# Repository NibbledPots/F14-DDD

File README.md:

# F14 DDP
PCB for the DDP/DDD of the F-14 RIO cockpit

You'll have to build and flash it yourself, the code can be found [here](https://github.com/NibbledPots/F14DDPcode)

Includes:
* RDR, IR, and IFF buttons
* PD and Pulse STT, PD Search, RWS, TWS Auto and Manual, and Pulse Search buttons 
* Buttons are in the general shape they are in in the cockpit, but they are not to scale

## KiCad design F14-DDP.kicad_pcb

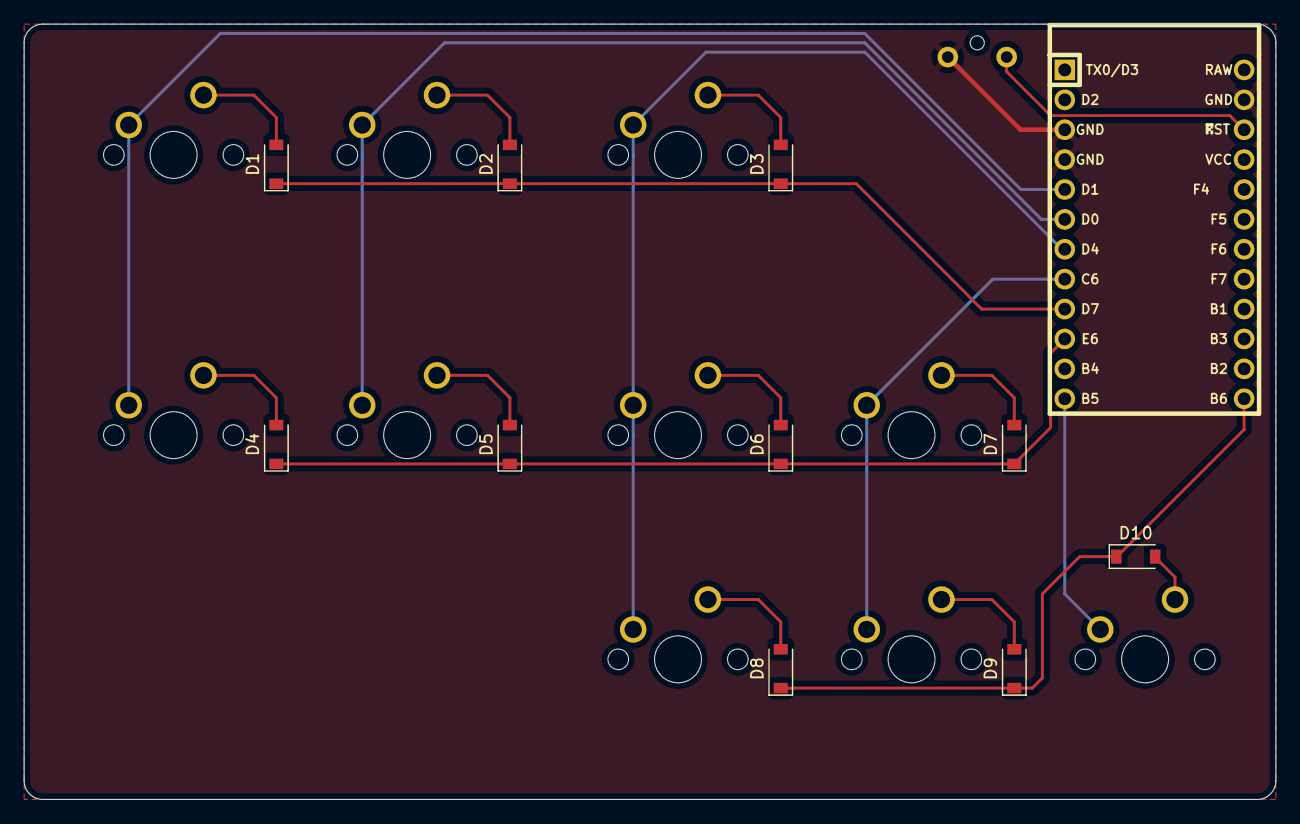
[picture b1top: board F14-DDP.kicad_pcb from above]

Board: 2 copper layers, 106.4 x 65.9 mm, 22 parts (1 on the bottom side), 20 nets.

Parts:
D1, D2, D3, D4, D5, D6, D7, D8, D9, D10: D_Small; D_SOD-123
MX1, MX2, MX3, MX4, MX5, MX6, MX7, MX8, MX9, MX10: MX-NoLED; MXOnly-1U-NoLED
SW1: SW_Push; SW_Tactile_SPST_Angled_MJTP1117-no-mount
U1: ProMicro; ArduinoProMicro

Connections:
/COL0: MX1.1 (COL), MX4.1 (COL), U1.5 (2/PD1)
/COL1: MX2.1 (COL), MX5.1 (COL), U1.6 (3/PD0)
/COL2: MX3.1 (COL), MX6.1 (COL), MX8.1 (COL), U1.7 (4/PD4)
/COL3: MX7.1 (COL), MX9.1 (COL), U1.8 (5/PC6)
/COL4: MX10.1 (COL), U1.12 (9/PB5)
/ROW0: D1.1 (K), D2.1 (K), D3.1 (K), U1.9 (6/PD7)
/ROW1: D4.1 (K), D5.1 (K), D6.1 (K), D7.1 (K), U1.10 (7/PE6)
/ROW2: D8.1 (K), D9.1 (K), D10.1 (K), U1.13 (10/PB6)
GND: SW1.2, U1.3 (GND), U1.4 (GND), U1.23 (GND)
unnamed: D1.2 (A), MX1.2 (ROW)
unnamed: D2.2 (A), MX2.2 (ROW)
unnamed: D3.2 (A), MX3.2 (ROW)
unnamed: D4.2 (A), MX4.2 (ROW)
unnamed: D5.2 (A), MX5.2 (ROW)
unnamed: D6.2 (A), MX6.2 (ROW)
unnamed: D7.2 (A), MX7.2 (ROW)
unnamed: D8.2 (A), MX8.2 (ROW)
unnamed: D9.2 (A), MX9.2 (ROW)
unnamed: D10.2 (A), MX10.2 (ROW)
unnamed: SW1.1, U1.22 (RST)

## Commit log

2022-05-03 Initialize project
2022-05-03 Add submodules
2022-05-03 Added libraries
2022-05-03 added pro micro footprint
2022-05-03 added matrix
2022-05-03 footprints assigned and placed
2022-05-03 traces
2022-05-03 Decoration pt1
2022-05-03 Done!
2022-05-03 more beautification
2022-05-05 redid spacing and traces
2022-05-05 restored backup
2022-05-05 FIXED
2022-05-05 more deco
2022-05-05 back filling
2022-05-05 generated gerbers
2022-05-06 tweaking
2022-06-12 cleaned up traces
2022-06-12 edited fillings
2022-06-12 generated files
2022-07-22 v2 changes
2022-08-02 Revert "changes"
    This reverts commit db015a99a79353056ca954ad381e07df77b81b86.
2022-08-02 save
2022-08-02 Revert "generated files"
    This reverts commit bd5c26b90c5cd8bdc58e0abf7d9282f48b5f5a8e.
2022-08-02 reverted to V1
2022-09-12 added 3d models
2022-10-27 Added Rotary switch footprint and symbol
2022-10-27 Revert "Added Rotary switch footprint and symbol"
    This reverts commit 7d9337107d9ddfbfc9a550b76e0d99979b83cd6d.
